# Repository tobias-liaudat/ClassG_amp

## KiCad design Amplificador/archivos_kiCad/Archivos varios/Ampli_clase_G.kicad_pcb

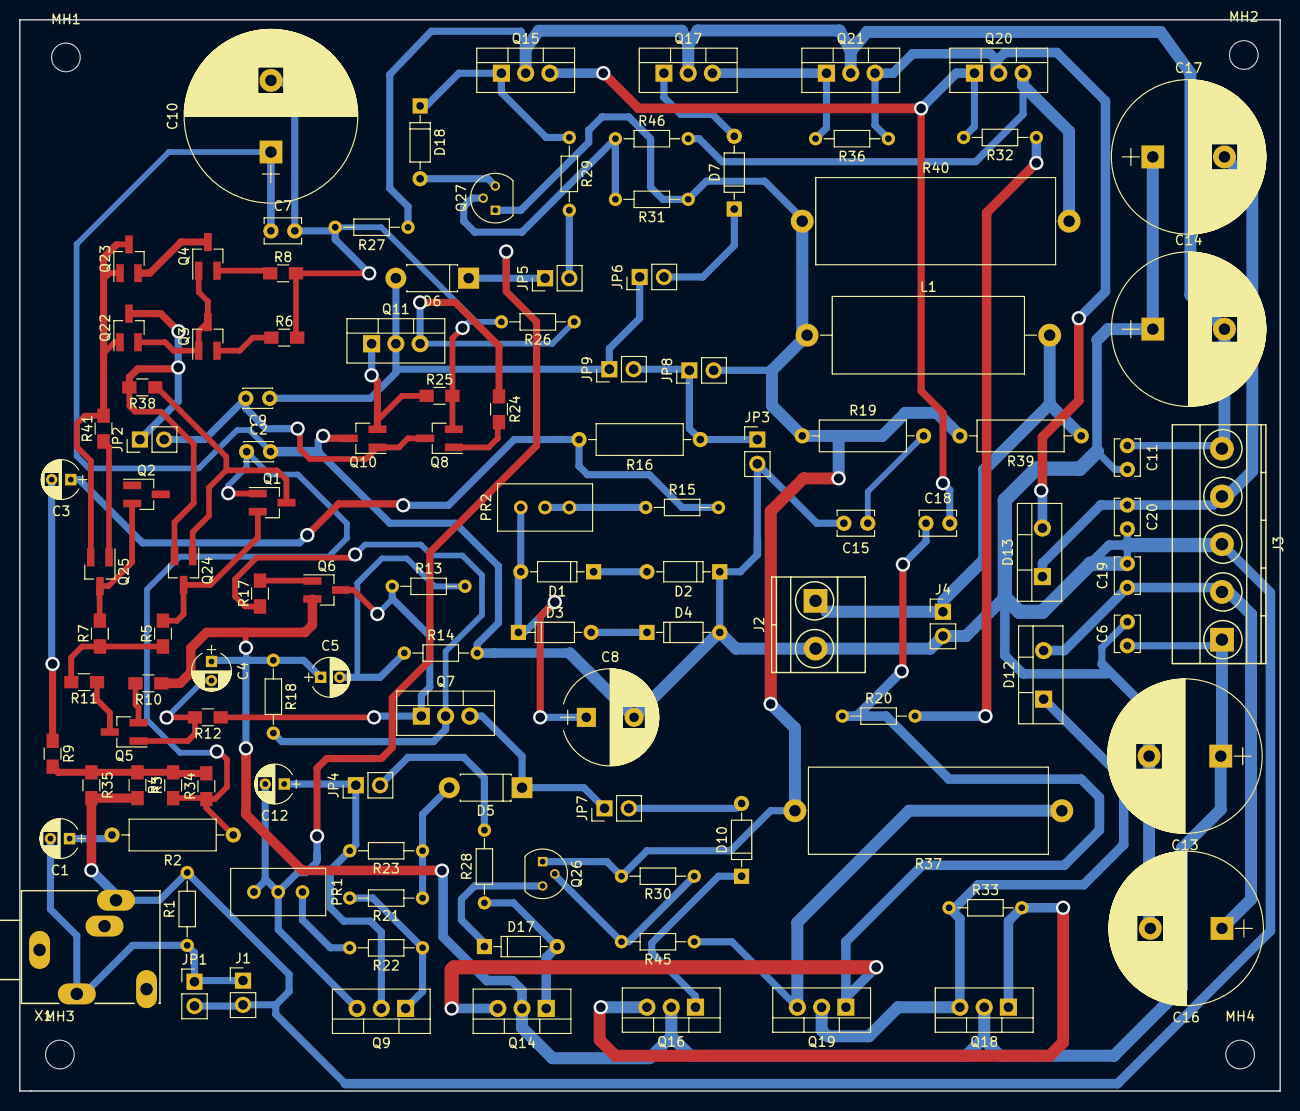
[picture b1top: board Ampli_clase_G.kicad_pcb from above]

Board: 2 copper layers, 132.0 x 112.1 mm, 121 parts (0 on the bottom side), 70 nets.

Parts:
C1, C4, C5, C12: 47u; CP_Radial_D4.0mm_P2.00mm
C2: 0.3n; C_Disc_D3.0mm_W2.0mm_P2.50mm
C3: 100u; CP_Radial_D4.0mm_P2.00mm
C6, C7, C11, C15, C18, C19, C20: 100n; C_Disc_D3.8mm_W2.6mm_P2.50mm
C8: 1000u; CP_Radial_D10.0mm_P5.00mm
C9: 33p; C_Disc_D3.0mm_W2.0mm_P2.50mm
C10: 1000u; CP_Radial_D18.0mm_P7.50mm
C13, C14, C16, C17: 220u; CP_Radial_D16.0mm_P7.50mm
D1, D2, D3, D4, D7, D10, D17, D18: 1N4148; D_DO-35_SOD27_P7.62mm_Horizontal
D5, D6: 1N4728; D_DO-41_SOD81_P7.62mm_Horizontal
D12, D13: MUR860; TO-220-2_Vertical
J1: Conn_IN; Pin_Header_Straight_1x02_Pitch2.54mm
J2: LOAD_CONN; TerminalBlock_Phoenix_MKDS1.5-2pol
J3: SUPPLY_CONN; TerminalBlock_Phoenix_MKDS1.5-5pol
J4: CONN_OUT; Pin_Header_Straight_1x02_Pitch2.54mm
JP1: Jumper_NO_Small; Pin_Header_Straight_1x02_Pitch2.54mm
JP2: Diff_Stage_Jumper; Pin_Header_Straight_1x02_Pitch2.54mm
JP3: Jumper_Q2; Pin_Header_Straight_1x02_Pitch2.54mm
JP4: Low_Pos_Jumper; Pin_Header_Straight_1x02_Pitch2.54mm
JP5: Low_Neg_Jumper; Pin_Header_Straight_1x02_Pitch2.54mm
JP6: High_Neg_Jumper; Pin_Header_Straight_1x02_Pitch2.54mm
JP7: High_Pos_Jumper; Pin_Header_Straight_1x02_Pitch2.54mm
JP8: Jumper_Feedback; Pin_Header_Straight_1x02_Pitch2.54mm
JP9: Jumper_2ndStage; Pin_Header_Straight_1x02_Pitch2.54mm
L1: 1u; L_Axial_L20.0mm_D8.0mm_P25.40mm_Horizontal
MH1, MH2, MH3, MH4: MountingHole_3mm
PR1: 1k; Potentiometer_Trimmer_Suntan_TSR-3386C_Vertical
PR2: 100; Potentiometer_Trimmer_Suntan_TSR-3386C_Vertical
Q1, Q2, Q5, Q6: BC856; SOT-23_Handsoldering
Q3, Q4, Q8, Q10, Q22, Q23, Q24, Q25: BC846; SOT-23_Handsoldering
Q7, Q9, Q11, Q14, Q16: 2SC4793; TO-220-3_Vertical
Q15, Q17: 2SA1837; TO-220-3_Vertical
Q18, Q19: 2SC5200; TO-220-3_Vertical
Q20, Q21: 2SA1943; TO-220-3_Vertical
Q26: MPSA42; TO-92_Molded_Narrow
Q27: MPSA92; TO-92_Molded_Narrow
R1: 100k; R_Axial_DIN0204_L3.6mm_D1.6mm_P7.62mm_Horizontal
R2, R19, R39: 10; R_Axial_DIN0309_L9.0mm_D3.2mm_P12.70mm_Horizontal
R3, R4, R11, R12, R17, R24, R25, R34, R35, R38, R41: 2.2k; R_0805_HandSoldering
R5, R7, R9, R10: 100; R_0805_HandSoldering
R6, R8: 68; R_0805_HandSoldering
R13, R14: 10k; R_Axial_DIN0204_L3.6mm_D1.6mm_P7.62mm_Horizontal
R15: 51; R_Axial_DIN0204_L3.6mm_D1.6mm_P7.62mm_Horizontal
R16: 2.2k; R_Axial_DIN0309_L9.0mm_D3.2mm_P12.70mm_Horizontal
R18: 33; R_Axial_DIN0204_L3.6mm_D1.6mm_P7.62mm_Horizontal
R20, R28, R29, R32, R33, R36, R46: 100; R_Axial_DIN0204_L3.6mm_D1.6mm_P7.62mm_Horizontal
R21: 3.3k; R_Axial_DIN0204_L3.6mm_D1.6mm_P7.62mm_Horizontal
R22: 390; R_Axial_DIN0204_L3.6mm_D1.6mm_P7.62mm_Horizontal
R23: 16; R_Axial_DIN0204_L3.6mm_D1.6mm_P7.62mm_Horizontal
R26, R27: 10; R_Axial_DIN0204_L3.6mm_D1.6mm_P7.62mm_Horizontal
R30: 560; R_Axial_DIN0204_L3.6mm_D1.6mm_P7.62mm_Horizontal
R31: 180; R_Axial_DIN0204_L3.6mm_D1.6mm_P7.62mm_Horizontal
R37, R40: 0.22; R_Axial_Power_L25.0mm_W9.0mm_P27.94mm
R45: 330; R_Axial_DIN0204_L3.6mm_D1.6mm_P7.62mm_Horizontal
X1: Jack_IN; Stereo_Jack_3.5mm_Switch_Ledino_KB3SPRS

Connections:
+VCC_15V: C16.1, C19.1, D12.2, J3.2
+VCC_40V: C4.1, C5.1, C6.1, C13.1, J3.1, Q6.2, Q14.2, Q16.2, Q18.2, R10.1, R18.1
GND: C2.2, C6.2, C7.1, C8.2, C10.1, C11.2, C13.2, C14.1, C15.2, C16.2, C17.1, C19.2, C20.2, D2.1, D4.2, J1.2, J2.2, J3.3, J4.2, JP1.2, JP3.2, Q10.3, R1.2, R4.2, R14.2, R35.2, X1.2
unnamed: C1.1, R2.2
unnamed: C1.2, J1.1, JP1.1, R1.1, X1.1
unnamed: C2.1, Q1.1, R2.1, R3.1, R34.1
unnamed: C3.1, Q2.1, R15.2, R16.2
unnamed: C3.2, R9.1
unnamed: C4.2, Q5.1, R12.2
unnamed: C5.2, R13.2, R14.1
unnamed: C8.1, D1.2, D3.1, PR2.1
unnamed: C9.1, D6.2, JP6.1, JP9.1, Q11.2
unnamed: C9.2, JP2.2, Q8.3, Q10.1
unnamed: C7.2, C10.2, Q8.2, R6.2, R8.2, R25.2, R26.2, R27.2
unnamed: C12.1, JP4.1, Q9.2, R23.2
unnamed: C12.2, D6.1, JP5.1, PR1.2, PR1.3, Q9.3
unnamed: C15.1, R19.2
unnamed: C18.1, Q14.3, Q19.1, R20.1
unnamed: C18.2, Q15.3, Q20.1, R32.2
unnamed: D1.1, D2.2
unnamed: D3.2, D4.1
unnamed: D5.1, JP7.1, Q7.3
unnamed: D5.2, R21.1, R23.1
unnamed: D7.1, JP6.2
unnamed: D7.2, Q17.1
unnamed: D10.1, Q16.1
unnamed: D10.2, JP7.2
unnamed: D12.1, Q18.3, Q19.2, R33.1
unnamed: D13.2, Q20.2, Q21.3, R36.1
unnamed: D17.1, Q26.3
unnamed: D17.2, Q14.1, R28.1
unnamed: D18.1, Q15.1, R29.1
unnamed: D18.2, Q27.3
unnamed: J2.1, J4.1, L1.2, R39.1
unnamed: JP2.1, Q22.3, Q24.2, R38.2
unnamed: JP3.1, JP8.1, JP9.2, R16.1
unnamed: JP4.2, R28.2
unnamed: JP5.2, R29.2
unnamed: JP8.2, L1.1, Q26.1, Q27.1, R19.1, R30.2, R31.1, R37.2, R39.2, R40.1
unnamed: PR1.1, R22.2
unnamed: PR2.2, PR2.3, R15.1
unnamed: Q1.2, Q24.3, R5.2
unnamed: Q1.3, Q24.1, R38.1
unnamed: Q2.2, Q25.3, R7.2
unnamed: Q2.3, Q25.1, R41.1
unnamed: Q3.2, R6.1
unnamed: Q4.2, R8.1
unnamed: Q5.2, R10.2
unnamed: Q5.3, R11.1
unnamed: Q6.1, R17.2
unnamed: Q6.3, Q7.1, R12.1, R13.1
unnamed: Q7.2, R17.1, R18.2
unnamed: Q8.1, R24.2
unnamed: Q9.1, R21.2, R22.1
unnamed: Q10.2, Q11.1, R25.1
unnamed: Q11.3, R24.1, R26.1
unnamed: Q16.3, Q18.1, R33.2
unnamed: Q17.3, Q21.1, R36.2
unnamed: Q19.3, R37.1, R45.1
unnamed: Q20.3, R40.2, R46.2
unnamed: Q22.1, Q23.1, Q23.3, Q25.2, R41.2
unnamed: Q3.1, Q3.3, Q4.1, Q22.2
unnamed: Q4.3, Q23.2
unnamed: Q26.2, R30.1, R45.2
unnamed: Q27.2, R31.2, R46.1
unnamed: R3.2, R4.1, R9.2, R34.2, R35.1
unnamed: R5.1, R7.1, R11.2
unnamed: R20.2, R32.1
VEE_-15V: C17.2, C20.1, D13.1, J3.4
VEE_-40V: C11.1, C14.2, J3.5, Q15.2, Q17.2, Q21.2, R27.1
